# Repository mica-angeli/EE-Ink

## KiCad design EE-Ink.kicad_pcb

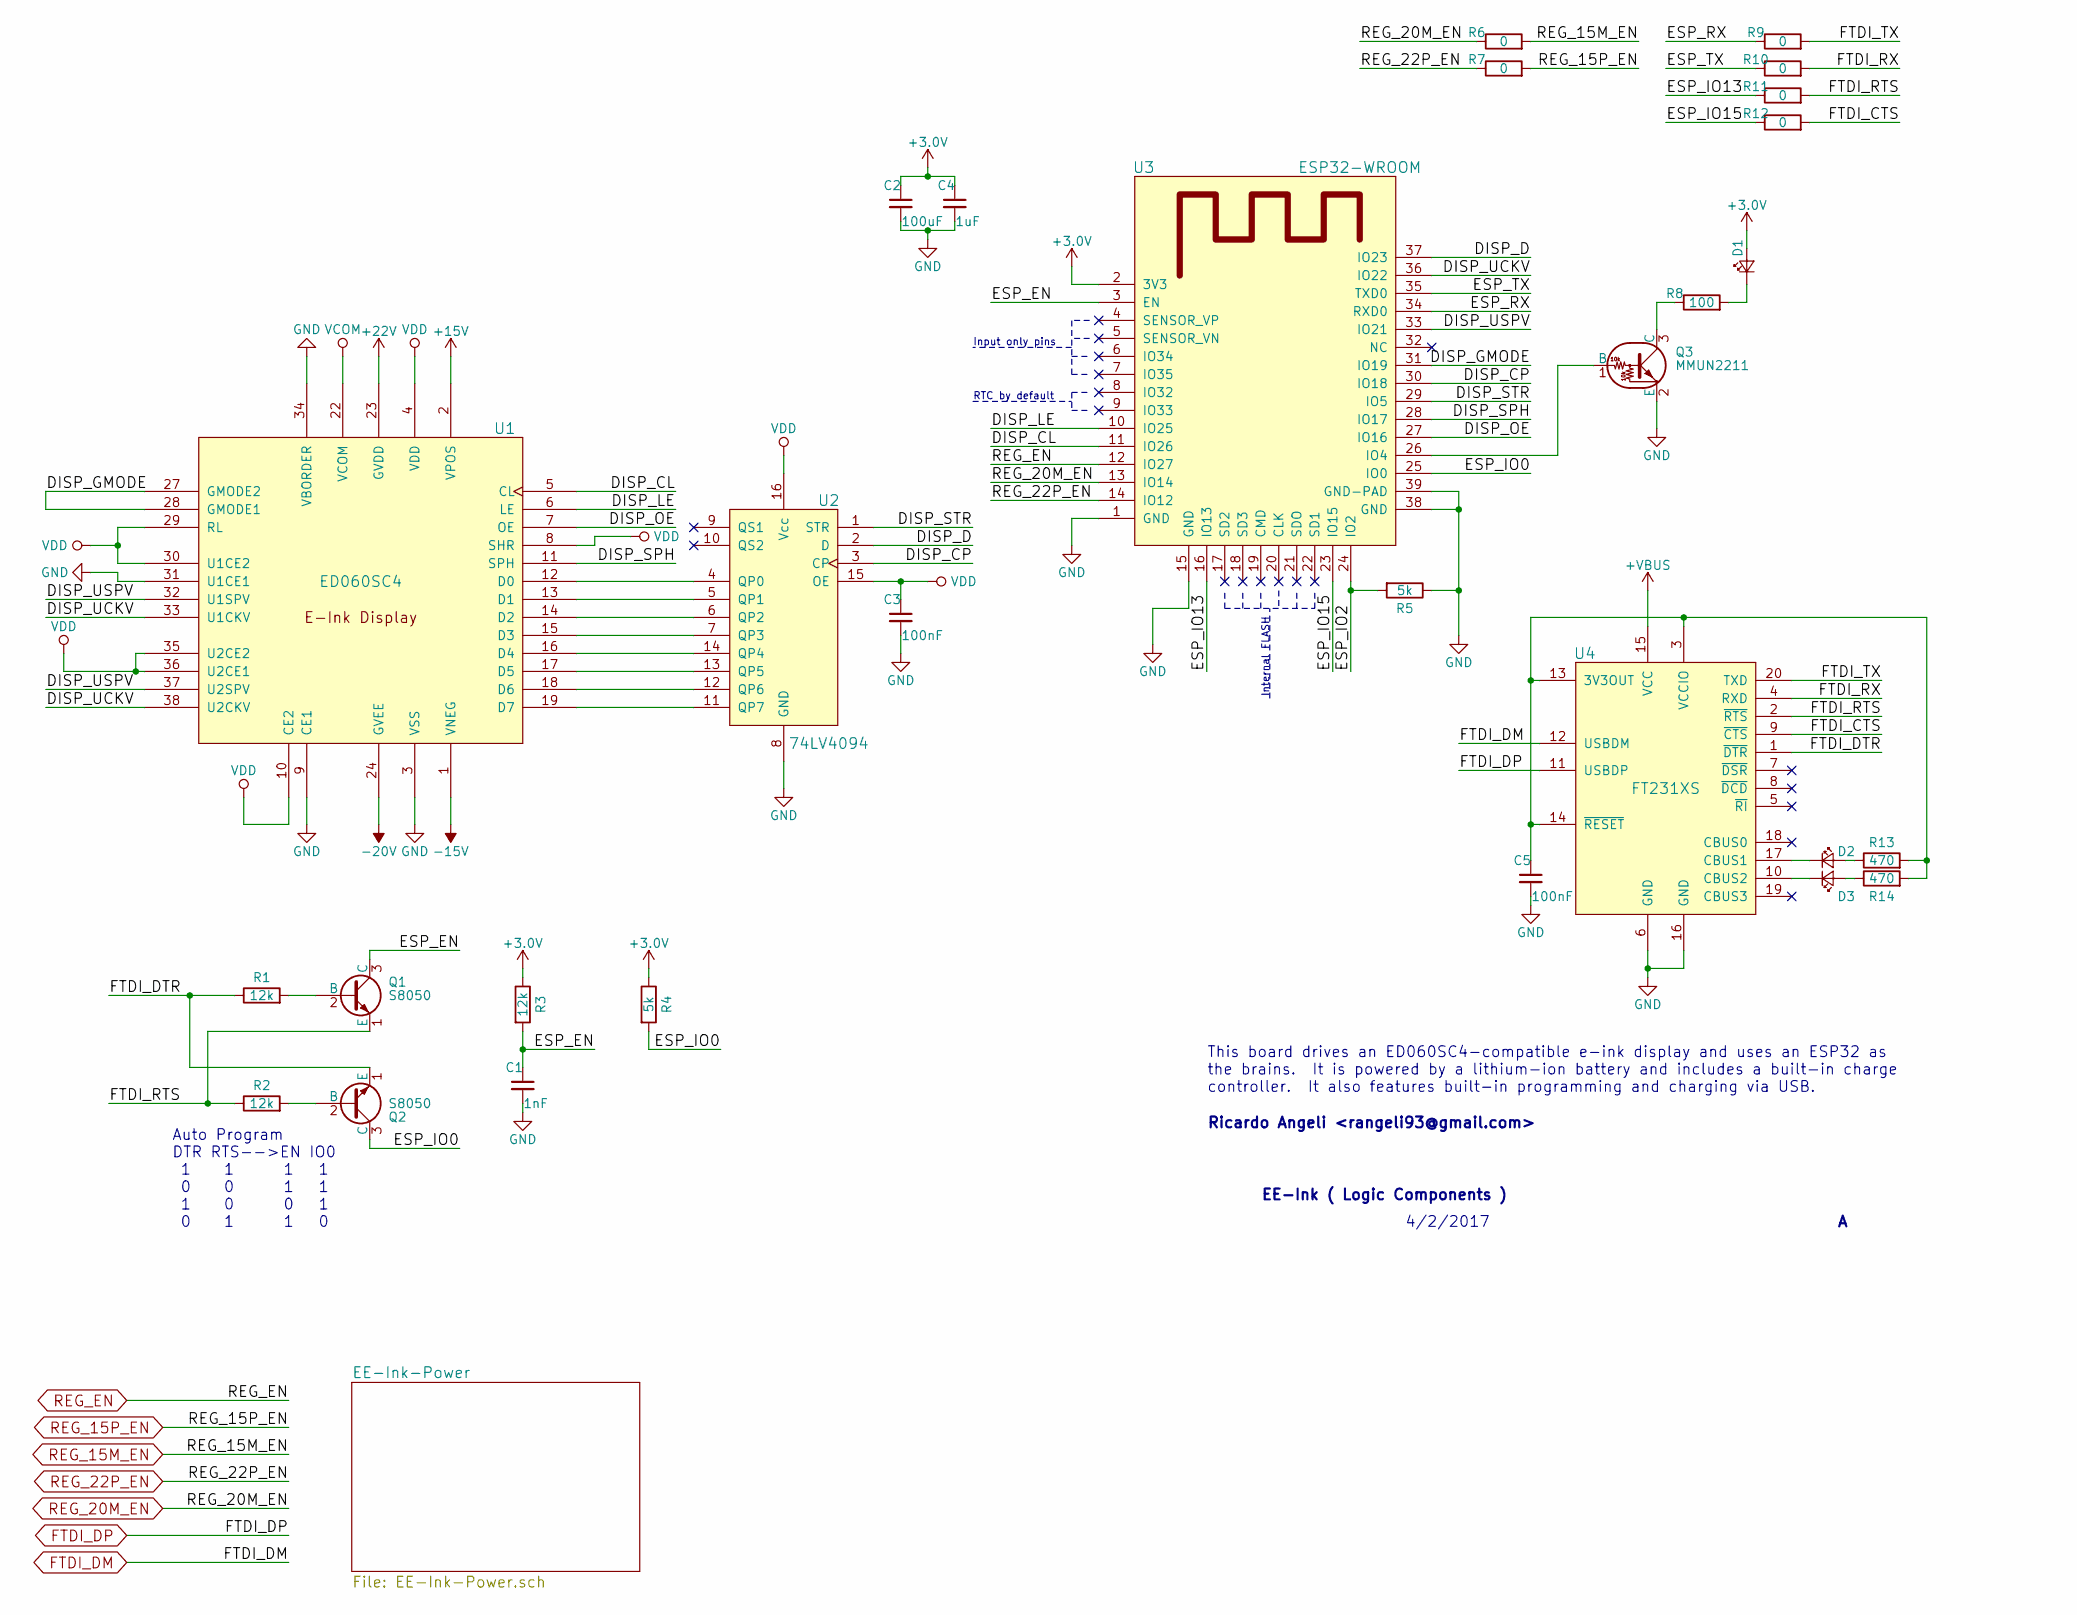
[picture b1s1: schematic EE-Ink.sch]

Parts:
C1: 1nF; C_0805
C2: 100uF; C_1206
C3, C5: 100nF; C_0805
C4: 1uF; C_0805
D1, D2, D3: LED_Small; LED_0805
Q1, Q2: S8050; TO-92_Molded_Narrow
Q3: MMUN2211; SOT-23
R1, R2, R3: 12k; R_0805
R4, R5: 5k; R_0805
R6, R7, R9, R10, R11, R12: 0; R_0805
R8: 100; R_0805
R13, R14: 470; R_0805
U1: ED060SC4; HIROSE_FH26-39-PIN-0.3mm
U2: 74LV4094; TSSOP-16_4.4x5mm_Pitch0.65mm
U3: ESP32-WROOM
U4: FT231XS; SSOP-20_4.4x6.5mm_Pitch0.65mm

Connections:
+3.0V: C2.1, C4.1, D1.2 (A), R3.1, R4.1, U3.2 (3V3); also elsewhere on the board
+15V: U1.2 (VPOS); also elsewhere on the board
+22V: U1.23 (GVDD); also elsewhere on the board
+VBUS: U4.15 (VCC); also elsewhere on the board
-15V: U1.1 (VNEG); also elsewhere on the board
-20V: U1.24 (GVEE); also elsewhere on the board
/DISP_CL: U1.5 (CL), U3.11 (IO26)
/DISP_CP: U2.3 (CP), U3.30 (IO18)
/DISP_D: U2.2 (D), U3.37 (IO23)
/DISP_GMODE: U1.27 (GMODE2), U1.28 (GMODE1), U3.31 (IO19)
/DISP_LE: U1.6 (LE), U3.10 (IO25)
/DISP_OE: U1.7 (OE), U3.27 (IO16)
/DISP_SPH: U1.11 (SPH), U3.28 (IO17)
/DISP_STR: U2.1 (STR), U3.29 (IO5)
/DISP_UCKV: U1.33 (U1CKV), U1.38 (U2CKV), U3.36 (IO22)
/DISP_USPV: U1.32 (U1SPV), U1.37 (U2SPV), U3.33 (IO21)
/ESP_EN: C1.1, Q1.3 (C), R3.2, U3.3 (EN)
/ESP_IO0: Q2.3 (C), R4.2, U3.25 (IO0)
/ESP_IO2: R5.2, U3.24 (IO2)
/ESP_IO13: R11.1, U3.16 (IO13)
/ESP_IO15: R12.1, U3.23 (IO15)
/ESP_RX: R9.1, U3.34 (RXD0)
/ESP_TX: R10.1, U3.35 (TXD0)
/FTDI_CTS: R12.2, U4.9 (~CTS)
/FTDI_DTR: Q2.1 (E), R1.1, U4.1 (~DTR)
/FTDI_RTS: Q1.1 (E), R2.1, R11.2, U4.2 (~RTS)
/FTDI_RX: R10.2, U4.4 (RXD)
/FTDI_TX: R9.2, U4.20 (TXD)
FTDI_DM: U4.12 (USBDM); also elsewhere on the board
FTDI_DP: U4.11 (USBDP); also elsewhere on the board
GND: C1.2, C2.2, C3.2, C4.2, C5.2, Q3.2 (E), R5.1, U1.3 (VSS), U1.9 (CE1), U1.31 (U1CE1), U1.34 (VBORDER), U2.8 (GND), U3.1 (GND), U3.15 (GND), U3.38 (GND), U3.39 (GND-PAD), U4.6 (GND), U4.16 (GND); also elsewhere on the board
unnamed: C5.1, R13.2, R14.2, U4.3 (VCCIO), U4.13 (3V3OUT), U4.14 (~RESET)
unnamed: D1.1 (K), R8.2
unnamed: D2.1 (K), U4.17 (CBUS1)
unnamed: D2.2 (A), R13.1
unnamed: D3.1 (K), U4.10 (CBUS2)
unnamed: D3.2 (A), R14.1
unnamed: Q1.2 (B), R1.2
unnamed: Q2.2 (B), R2.2
unnamed: Q3.1 (B), U3.26 (IO4)
unnamed: Q3.3 (C), R8.1
unnamed: U1.12 (D0), U2.4 (QP0)
unnamed: U1.13 (D1), U2.5 (QP1)
unnamed: U1.14 (D2), U2.6 (QP2)
unnamed: U1.15 (D3), U2.7 (QP3)
unnamed: U1.16 (D4), U2.14 (QP4)
unnamed: U1.17 (D5), U2.13 (QP5)
unnamed: U1.18 (D6), U2.12 (QP6)
unnamed: U1.19 (D7), U2.11 (QP7)
REG_15M_EN: R6.2; also elsewhere on the board
REG_15P_EN: R7.2; also elsewhere on the board
REG_20M_EN: R6.1, U3.13 (IO14); also elsewhere on the board
REG_22P_EN: R7.1, U3.14 (IO12); also elsewhere on the board
REG_EN: U3.12 (IO27); also elsewhere on the board
VCOM: U1.22 (VCOM); also elsewhere on the board
VDD: C3.1, U1.4 (VDD), U1.8 (SHR), U1.10 (CE2), U1.29 (RL), U1.30 (U1CE2), U1.35 (U2CE2), U1.36 (U2CE1), U2.15 (OE), U2.16 (Vcc); also elsewhere on the board

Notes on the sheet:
Auto Program DTR RTS-->EN IO0 1 1 1 1 0 0 1 1 1 0 0 1 0 1 1 0
EE-Ink ( Logic Components )
4/2/2017
This board drives an ED060SC4-compatible e-ink display and uses an ESP32 as the brains. It is powered by a lithium-ion battery and includes a built-in charge controller. It also features built-in programming and charging via USB.
Ricardo Angeli <rangeli93@gmail.com>
Input only pins
RTC by default
Internal FLASH

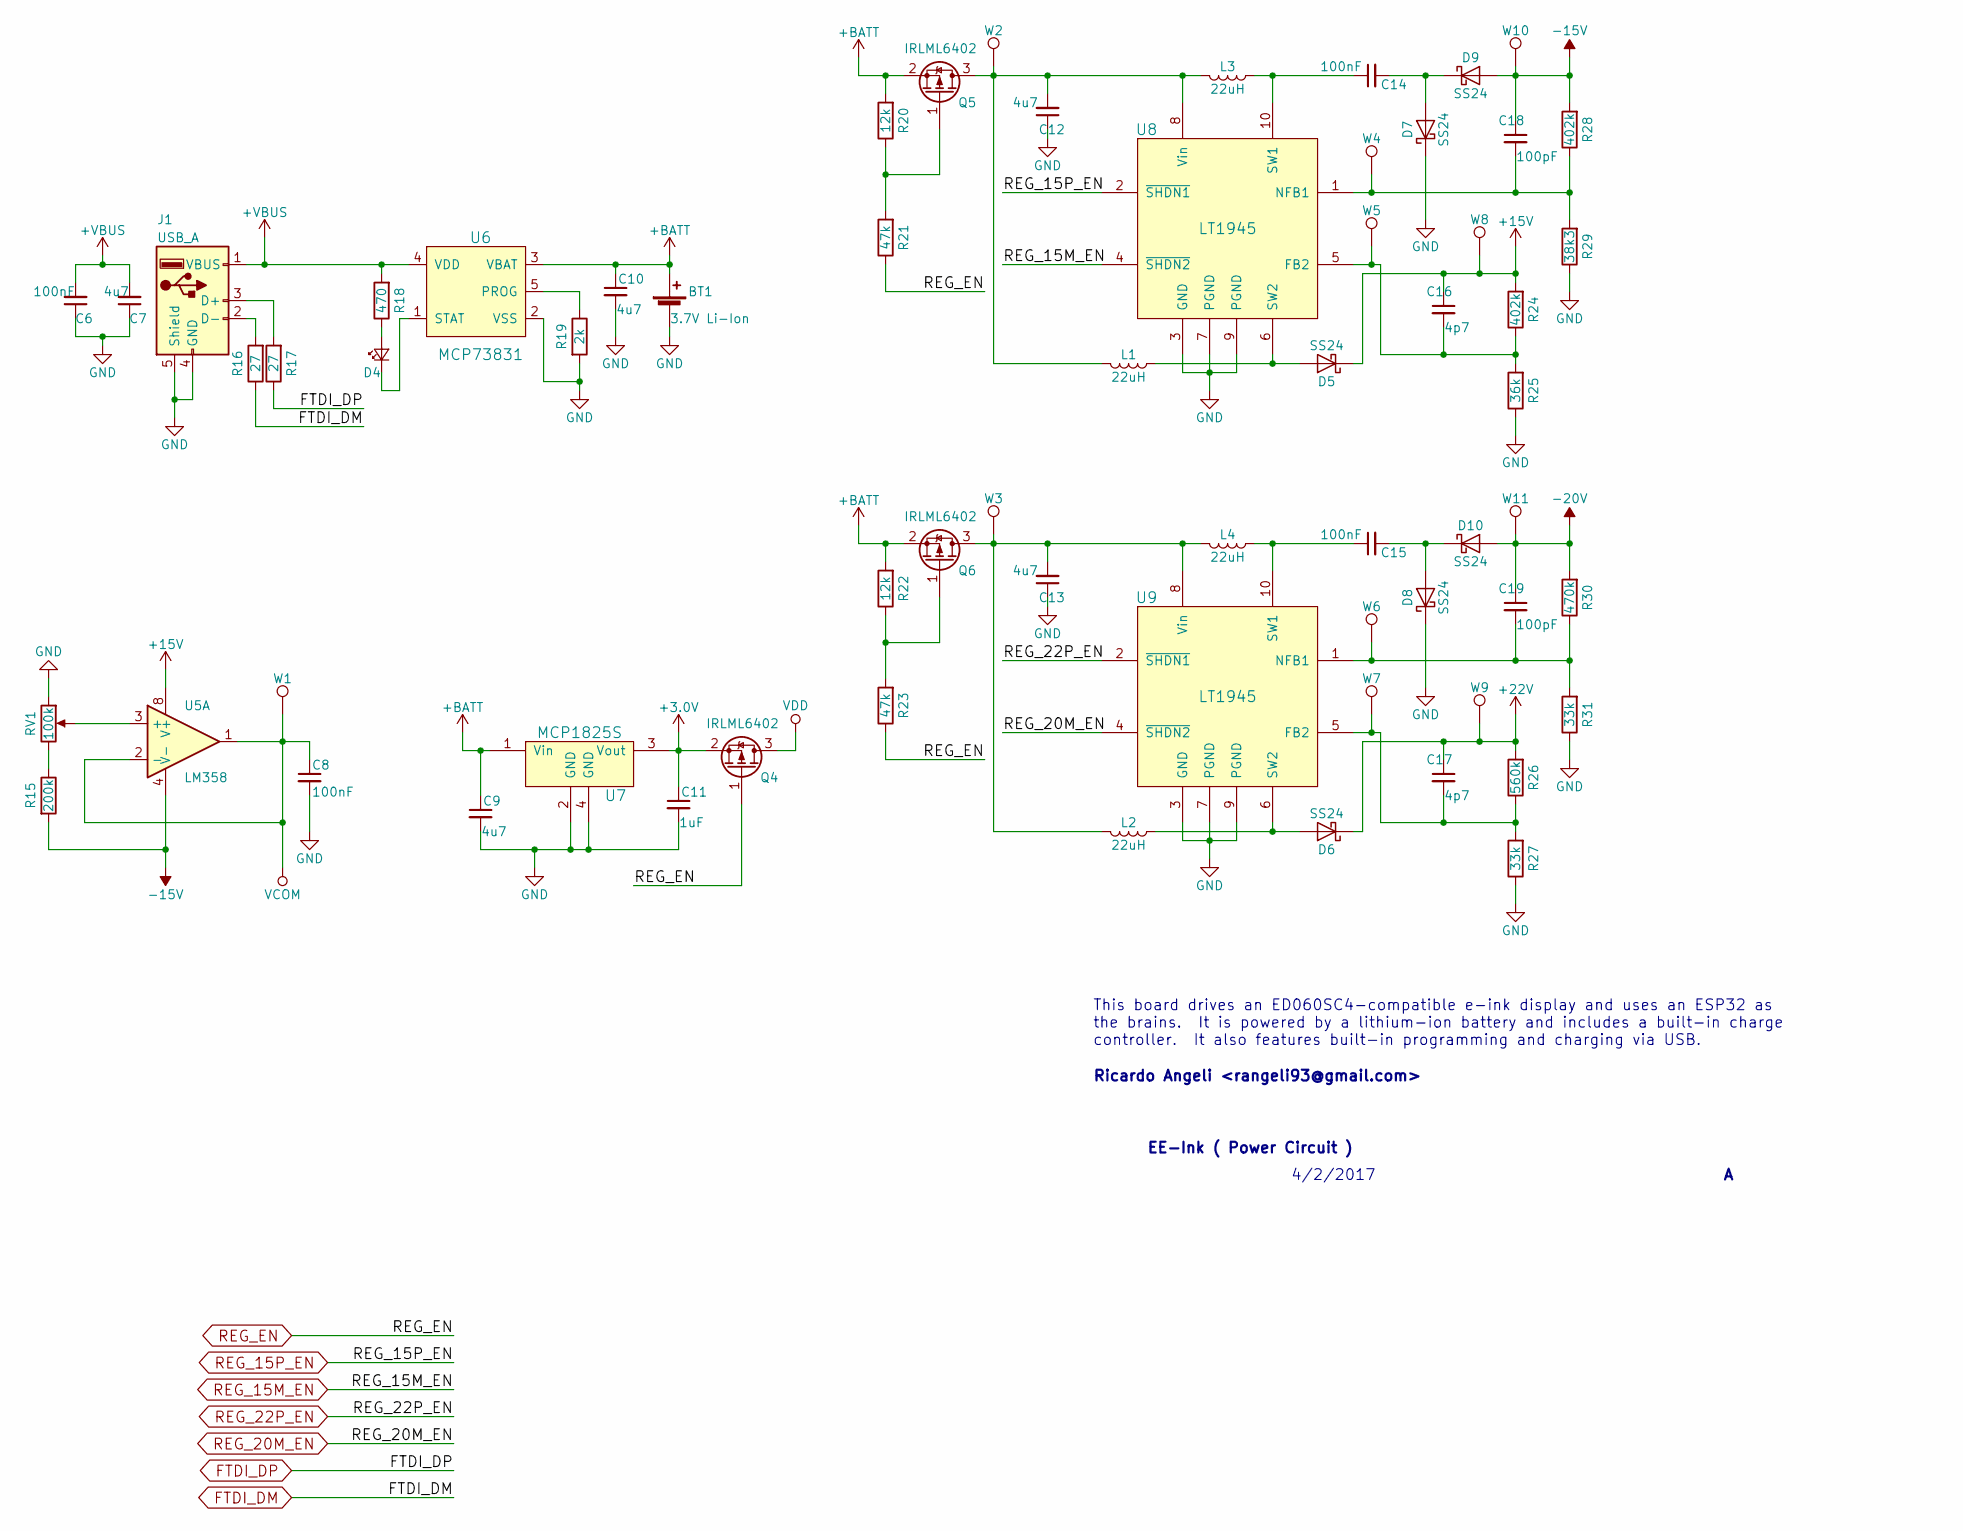
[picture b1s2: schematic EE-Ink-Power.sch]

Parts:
BT1: 3.7V Li-Ion
C6, C8, C14, C15: 100nF; C_0805
C7, C9, C10, C12, C13: 4u7; C_0805
C11: 1uF; C_0805
C16, C17: 4p7; C_0805
C18, C19: 100pF; C_0805
D4: LED_Small; LED_0805
D5, D6, D7, D8, D9, D10: SS24; DO-214AA
J1: USB_A; SMT-Micro-USB-AB
L1, L2, L3, L4: 22uH; R_0805
Q4, Q5, Q6: IRLML6402; SOT-23
R15: 200k; R_0805
R16, R17: 27; R_0805
R18: 470; R_0805
R19: 2k; R_0805
R20, R22: 12k; R_0805
R21, R23: 47k; R_0805
R24, R28: 402k; R_0805
R25: 36k; R_0805
R26: 560k; R_0805
R27, R31: 33k; R_0805
R29: 38k3; R_0805
R30: 470k; R_0805
RV1: 100k; TT-Electronics_Pot_23B
U5: LM358; SOIC-8_3.9x4.9mm_Pitch1.27mm
U6: MCP73831; SOT-23-5
U7: MCP1825S; SOT-223
U8, U9: LT1945; MSOP-10_3x3mm_Pitch0.5mm
W1, W2, W3, W4, W5, W6, W7, W8, W9, W10, W11: TEST_1P

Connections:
+3.0V: C11.1, Q4.2 (S), U7.3 (Vout); also elsewhere on the board
+15V: C16.1, D5.1 (K), R24.2, U5.8 (V+), W8.1; also elsewhere on the board
+22V: C17.1, D6.1 (K), R26.2, W9.1; also elsewhere on the board
+BATT: BT1.1 (+), C9.1, C10.1, Q5.2 (S), Q6.2 (S), R20.2, R22.2, U6.3 (VBAT), U7.1 (Vin)
+VBUS: C6.2, C7.2, J1.1 (VBUS), R18.2, U6.4 (VDD); also elsewhere on the board
-15V: C18.1, D9.2 (A), R15.2, R28.2, U5.4 (V-), W10.1; also elsewhere on the board
-20V: C19.1, D10.2 (A), R30.2, W11.1; also elsewhere on the board
FTDI_DM: R16.1; also elsewhere on the board
FTDI_DP: R17.1; also elsewhere on the board
GND: BT1.2 (-), C6.1, C7.1, C8.2, C9.2, C10.2, C11.2, C12.1, C13.1, D7.1 (K), D8.1 (K), J1.4 (GND), J1.5 (Shield), R19.2, R25.1, R27.1, R29.1, R31.1, RV1.1, U6.2 (VSS), U7.2 (GND), U7.4 (GND), U8.3 (GND), U8.7 (PGND), U8.9 (PGND), U9.3 (GND), U9.7 (PGND), U9.9 (PGND); also elsewhere on the board
unnamed: C12.2, L1.2, L3.2, Q5.3 (D), U8.8 (Vin), W2.1
unnamed: C13.2, L2.2, L4.2, Q6.3 (D), U9.8 (Vin), W3.1
unnamed: C14.1, L3.1, U8.10 (SW1)
unnamed: C14.2, D7.2 (A), D9.1 (K)
unnamed: C15.1, L4.1, U9.10 (SW1)
unnamed: C15.2, D8.2 (A), D10.1 (K)
unnamed: C16.2, R24.1, R25.2, U8.5 (FB2), W5.1
unnamed: C17.2, R26.1, R27.2, U9.5 (FB2), W7.1
unnamed: C18.2, R28.1, R29.2, U8.1 (NFB1), W4.1
unnamed: C19.2, R30.1, R31.2, U9.1 (NFB1), W6.1
unnamed: D4.1 (K), U6.1 (STAT)
unnamed: D4.2 (A), R18.1
unnamed: D5.2 (A), L1.1, U8.6 (SW2)
unnamed: D6.2 (A), L2.1, U9.6 (SW2)
unnamed: J1.2 (D-), R16.2
unnamed: J1.3 (D+), R17.2
unnamed: Q5.1 (G), R20.1, R21.2
unnamed: Q6.1 (G), R22.1, R23.2
unnamed: R15.1, RV1.3
unnamed: R19.1, U6.5 (PROG)
unnamed: RV1.2, U5.3 (+)
REG_15M_EN: U8.4 (~SHDN2); also elsewhere on the board
REG_15P_EN: U8.2 (~SHDN1); also elsewhere on the board
REG_20M_EN: U9.4 (~SHDN2); also elsewhere on the board
REG_22P_EN: U9.2 (~SHDN1); also elsewhere on the board
REG_EN: Q4.1 (G), R21.1, R23.1; also elsewhere on the board
VCOM: C8.1, U5.1, U5.2 (-), W1.1; also elsewhere on the board
VDD: Q4.3 (D); also elsewhere on the board

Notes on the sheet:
EE-Ink ( Power Circuit )
This board drives an ED060SC4-compatible e-ink display and uses an ESP32 as the brains. It is powered by a lithium-ion battery and includes a built-in charge controller. It also features built-in programming and charging via USB.
Ricardo Angeli <rangeli93@gmail.com>
4/2/2017

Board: 2 copper layers, 93 parts (0 on the bottom side), 78 nets, no tracks yet.

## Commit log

2017-03-24 Created empty KiCad project
2017-03-25 Added microcontroller and flash memory.
2017-03-25 Created drawing for the E-ink display and plopped it onto the schematic.
2017-03-25 Added dc to dc converter component.
2017-03-26 Added battery charger component.
2017-03-26 Added several components.
2017-03-26 Added regulator component.
2017-03-26 Began creating connections in the schematic.
2017-03-26 Connected all wires to E-ink component.
2017-03-26 Minor changes to connections to display.
2017-03-26 Connected op-amp.
2017-03-26 Added ftdi chip and started wiring power circuitry.
2017-03-26 Wired up the FTDI and charging circuit.
2017-03-26 Wired up first boost circuit according to example.
2017-03-27 Minor changes.
2017-03-27 Wired up second dc-dc converter and connected related I/O to mcu.
2017-03-27 Added battery voltage measuring.
2017-03-27 Wired up power inputs for the mcu.
2017-03-27 Moved blocks around the schematic.
2017-03-27 Began re-arranging components to a second sheet.
2017-03-27 Finished re-arranging components between schematics.
2017-03-27 Moved some little things around and created netlist.
2017-03-29 Exported schematic
2017-03-31 Replaced STM32 mcu with the ESP32 WROOM module.
2017-03-31 Deleted now-unnecessary parts.
2017-03-31 Re-arranged components (namely the FTDI chip) and created new power symbols for 3v and VBUS.
2017-03-31 Updated regulator.
2017-04-01 Switched FTDI chip to one that supported the full handshaking necessary for the ESP32's programming mode.
2017-04-02 Fixing transistor connections and adding UART stuff.
2017-04-03 Began wiring up ESP32's IO pins.
2017-04-03 Finished wiring up ESP32 pins.
2017-04-03 Switched out the regulator for a 500ma one. Cleaned up a few things.
2017-04-03 Linked footprint to regulator schematic symbol.
2017-04-04 Changed ESP I/O pin assignments to now use a shift register for the display's data lines. This was caused by a couple pins found to be input only.
2017-04-04 Added status LED.
2017-04-04 Added some labels for the unused pins.
2017-04-04 PDF generation.
2017-04-09 Finished reviewing schematic. Re-annotated all components.
2017-04-09 Re-generated netlist and created BOM.
2017-04-09 Began linking footprints to the components.
2017-04-11 Created footprint for the connector of the E-ink display and linked it.
2017-04-11 Created footprint for trimpot.
2017-04-12 Finished linking all component footprints.
2017-04-12 Added and edited ESP32 footprint.
2017-04-12 Began laying out PCB by spreading out the components.
2017-04-12 Fixed footprint for S8050 transistors.
